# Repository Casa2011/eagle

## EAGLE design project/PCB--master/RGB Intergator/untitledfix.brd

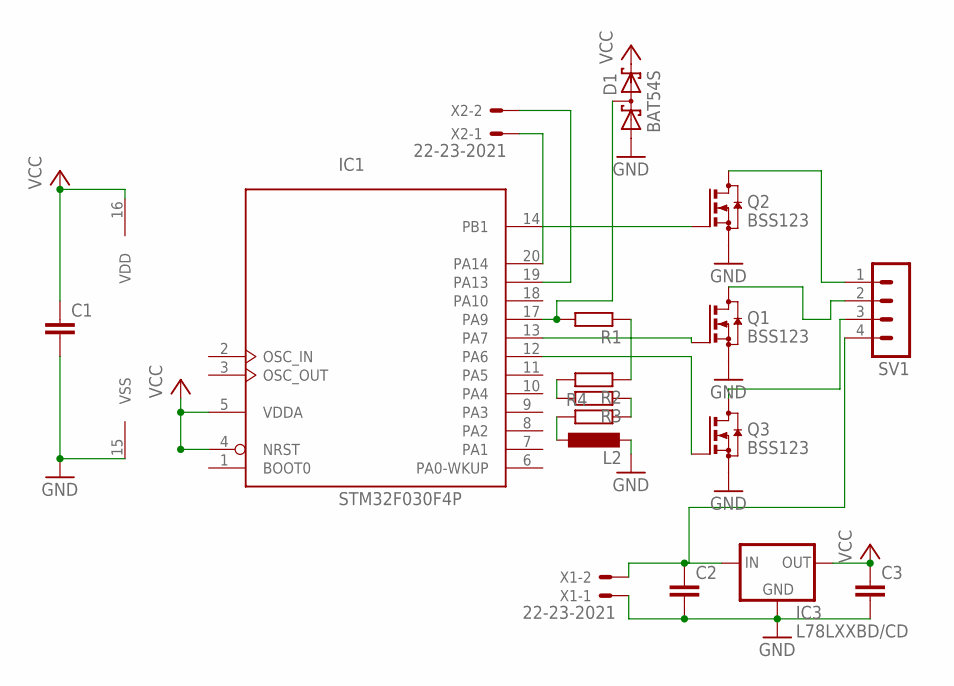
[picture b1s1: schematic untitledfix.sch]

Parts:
C1, C2, C3: C-EUC0805K; C0805K
D1: BAT54S; SOT23
IC1: STM32F030F4P; TSSOP20-I
IC3: L78LXXBD/CD; SO08
L2: L-EU0207/5V; 0207/5V
Q1, Q2, Q3: BSS123; SOT23
R1, R2, R3, R4: R-EU_M0805; M0805
SV1: MA04-1
X1, X2: 22-23-2021

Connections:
GND: C1.2, C2.2, C3.2, D1.1 (A1), IC1.15 (VSS), IC3.2 (GND1), IC3.3 (GND3), IC3.6 (GND4), IC3.7 (GND2), L2.2, Q1.2 (S), Q2.2 (S), Q3.2 (S), X1.1
unnamed: D1.3 (C1A2), IC1.17 (PA9), R1.2
unnamed: IC1.14 (PB1), Q2.1 (G)
unnamed: IC1.13 (PA7), Q1.1 (G)
unnamed: IC1.12 (PA6), Q3.1 (G)
unnamed: C2.1, IC3.8 (IN), SV1.4, X1.2
unnamed: R1.1, R2.1
unnamed: IC1.19 (PA13), X2.2
unnamed: Q3.3 (D), SV1.3
unnamed: Q1.3 (D), SV1.2
unnamed: Q2.3 (D), SV1.1
unnamed: IC1.20 (PA14), X2.1
unnamed: R2.2, R3.2
unnamed: R3.1, R4.2
unnamed: L2.1, R4.1
VCC: C1.1, C3.1, D1.2 (C2), IC1.4 (NRST), IC1.5 (VDDA), IC1.16 (VDD), IC3.1 (OUT)

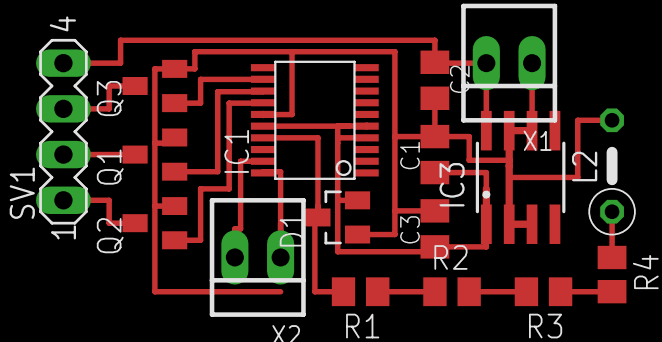
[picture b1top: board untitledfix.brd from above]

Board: 2 copper layers, 17 parts (0 on the bottom side), 16 nets.

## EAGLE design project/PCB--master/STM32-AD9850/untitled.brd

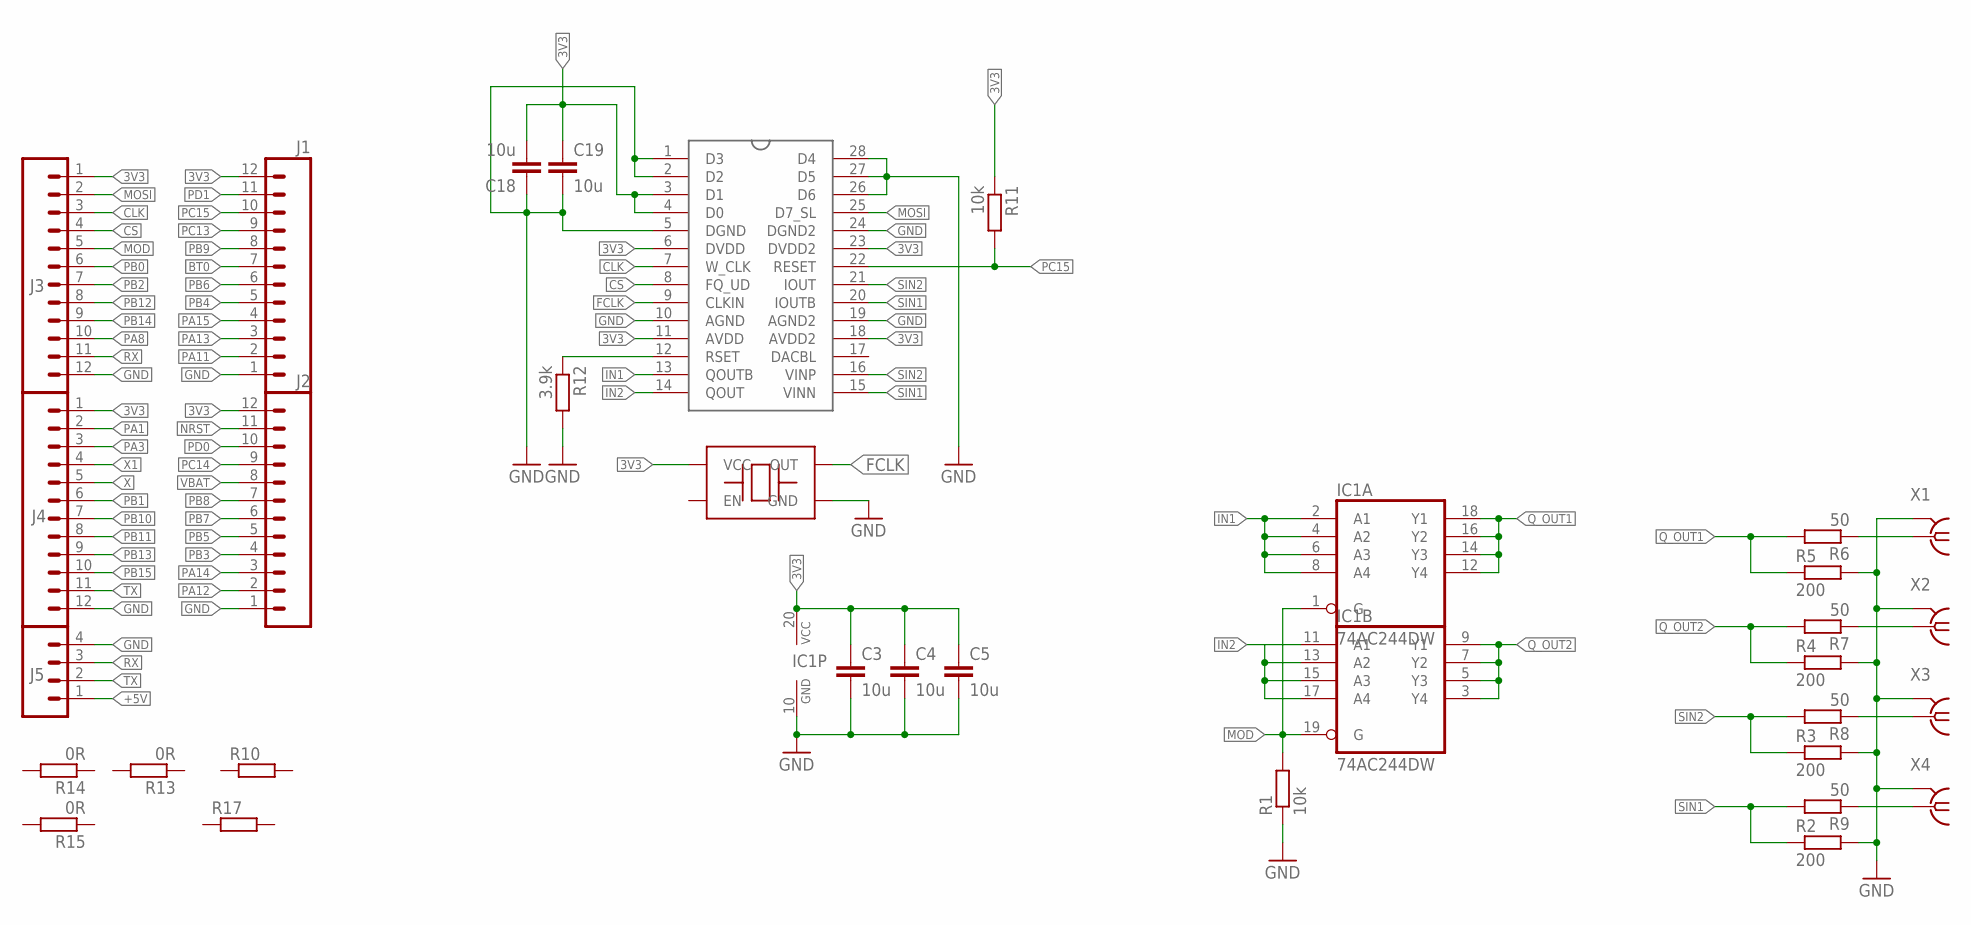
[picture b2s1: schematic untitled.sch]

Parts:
C3, C4, C5, C18, C19: 10u; 0805
IC1: 74AC244DW; SO20W
J1, J2, J3, J4: M12PTH; 1X12
J5: M04PTH; 1X04
R1, R11: 10k; 0805
R2, R3, R4, R5: 200; 0805
R6, R7, R8, R9: 50; 0805
R10: R0805; 0805
R12: 3.9k; 0805
R13, R15: 0R; 0805
R14: 0R; 1206
R17: R1206; 1206
U$1: AD9850; SSOP28
U$3: TXC-BA; 7X5
X1, X2, X3, X4: BU-SMA-H

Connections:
3V3: C3.1, C4.1, C5.1, C18.2, C19.1, IC1.20 (VCC), J1.12, J2.12, J3.1, J4.1, R11.1, U$1.3 (D1), U$1.4 (D0), U$1.6 (DVDD), U$1.11 (AVDD), U$1.18 (AVDD2), U$1.23 (DVDD2), U$3.VCC
+5V: J5.1
BT0: J1.7
CLK: J3.3, U$1.7 (W_CLK)
CS: J3.4, U$1.8 (FQ_UD)
FCLK: U$1.9 (CLKIN), U$3.OUT
GND: C3.2, C4.2, C5.2, C18.1, C19.2, IC1.10 (GND), J1.1, J2.1, J3.12, J4.12, J5.4, R1.1, R2.2, R3.2, R4.2, R5.2, R12.2, U$1.1 (D3), U$1.2 (D2), U$1.5 (DGND), U$1.10 (AGND), U$1.19 (AGND2), U$1.24 (DGND2), U$1.26 (D6), U$1.27 (D5), U$1.28 (D4), U$3.GND, X1.2, X1.3 (2), X1.4 (2), X1.5 (2), X2.2, X2.3 (2), X2.4 (2), X2.5 (2), X3.2, X3.3 (2), X3.4 (2), X3.5 (2), X4.2, X4.3 (2), X4.4 (2), X4.5 (2)
IN1: IC1.2 (A1), IC1.4 (A2), IC1.6 (A3), IC1.8 (A4), U$1.13 (QOUTB)
IN2: IC1.11 (A1), IC1.13 (A2), IC1.15 (A3), IC1.17 (A4), U$1.14 (QOUT)
MOD: IC1.1 (G), IC1.19 (G), J3.5, R1.2
MOSI: J3.2, U$1.25 (D7_SL)
unnamed: R6.1, X1.1
unnamed: R7.1, X2.1
unnamed: R8.1, X3.1
unnamed: R9.1, X4.1
NRST: J2.11
PA1: J4.2
PA3: J4.3
PA8: J3.10
PA11: J1.2
PA12: J2.2
PA13: J1.3
PA14: J2.3
PA15: J1.4
PB0: J3.6
PB1: J4.6
PB2: J3.7
PB3: J2.4
PB4: J1.5
PB5: J2.5
PB6: J1.6
PB7: J2.6
PB8: J2.7
PB9: J1.8
PB10: J4.7
PB11: J4.8
PB12: J3.8
PB13: J4.9
PB14: J3.9
PB15: J4.10
PC13: J1.9
PC14: J2.9
PC15: J1.10, R11.2, U$1.22 (RESET)
PD0: J2.10
PD1: J1.11
Q_OUT1: IC1.12 (Y4), IC1.14 (Y3), IC1.16 (Y2), IC1.18 (Y1), R5.1, R6.2
Q_OUT2: IC1.3 (Y4), IC1.5 (Y3), IC1.7 (Y2), IC1.9 (Y1), R4.1, R7.2
RX: J3.11, J5.3
R_SET: R12.1, U$1.12 (RSET)
SIN1: R2.1, R9.2, U$1.15 (VINN), U$1.20 (IOUTB)
SIN2: R3.1, R8.2, U$1.16 (VINP), U$1.21 (IOUT)
TX: J4.11, J5.2
VBAT: J2.8
X: J4.5
X1: J4.4

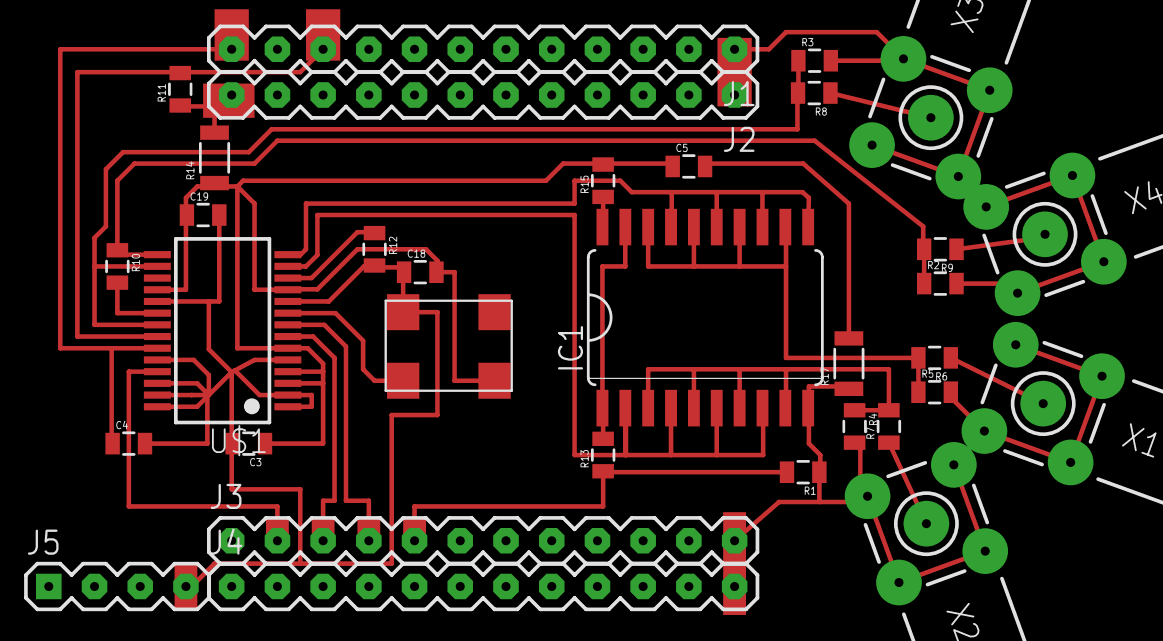
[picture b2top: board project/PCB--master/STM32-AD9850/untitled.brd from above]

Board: 2 copper layers, 33 parts (0 on the bottom side), 21 nets.

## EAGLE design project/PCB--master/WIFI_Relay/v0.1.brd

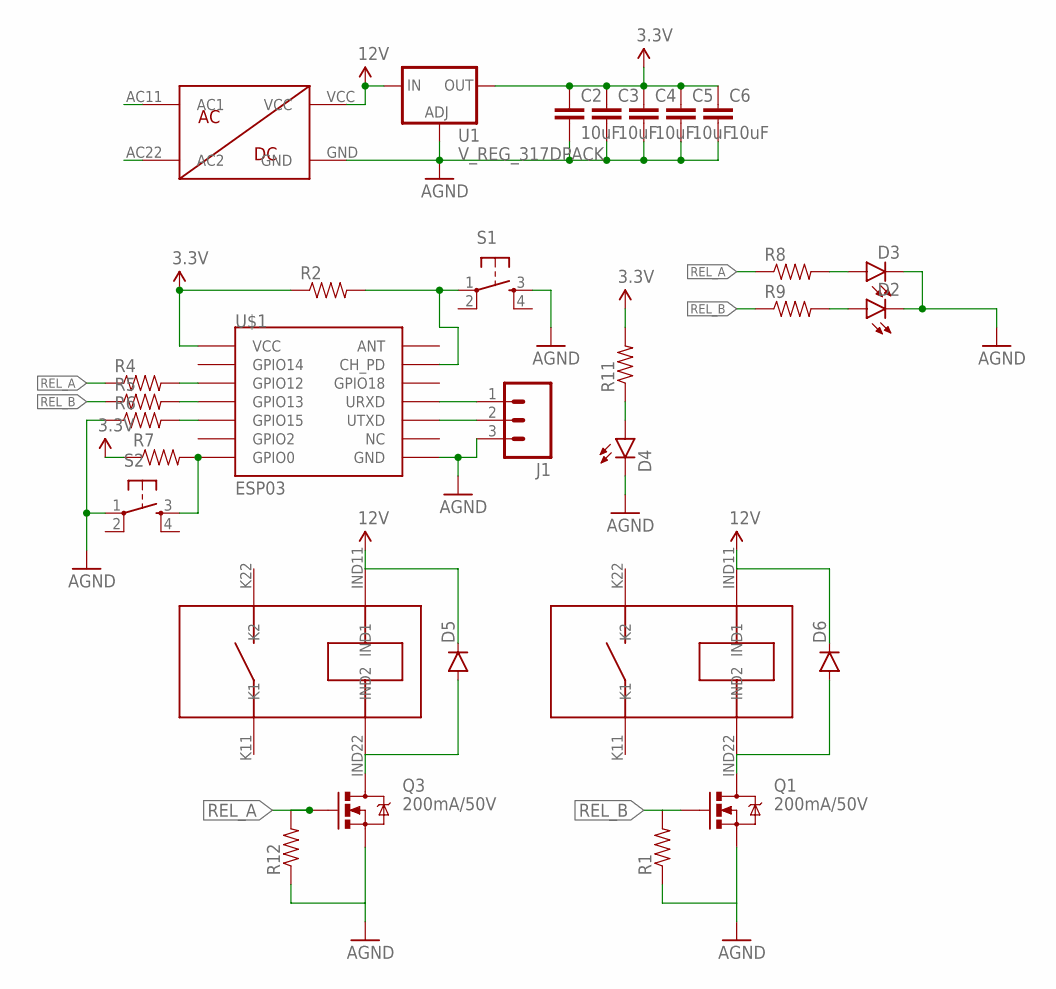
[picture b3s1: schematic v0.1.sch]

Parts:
C2, C3, C4, C5, C6: 10uF; 0603-CAP
D2, D3, D4: LED0603; LED-0603
D5, D6: DIODESOD123; SOD-123
J1: M03LONGPADS; 1X03_LONGPADS
Q1, Q3: 200mA/50V; SOT23-3
R1, R2, R4, R5, R6, R7, R8, R9, R11, R12: RESISTOR0805-RES; 0805
S1, S2: TAC_SWITCHPTH; TACTILE-PTH
U1: V_REG_317DPACK; V-REG_DPACK
U$1: ESP03
U$8: ACDC12V350MA
U$9, U$10: 302WP

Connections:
3.3V: C2.1, C3.1, C4.1, C5.1, C6.1, R2.1, R7.1, R11.2, U1.4 (OUT), U$1.VCC
12V: D5.C, D6.C, U1.3 (IN), U$8.VCC, U$9.IND11 (IND1), U$10.IND11 (IND1)
AGND: C2.2, C3.2, C4.2, C5.2, C6.2, D2.C, D3.C, D4.C, J1.3, Q1.2 (S), Q3.2 (S), R1.1, R6.1, R12.1, S1.3, S2.1, U1.1 (ADJ), U$1.GND, U$8.GND
unnamed: J1.1, U$1.URXD
unnamed: J1.2, U$1.UTXD
unnamed: D5.A, Q3.3 (D), U$10.IND22 (IND2)
unnamed: R2.2, S1.1, U$1.CH_PD
unnamed: R4.2, U$1.GPIO12
unnamed: R5.2, U$1.GPIO13
unnamed: R6.2, U$1.GPIO15
unnamed: D3.A, R8.2
unnamed: D2.A, R9.2
unnamed: R7.2, S2.3, U$1.GPIO0
unnamed: D4.A, R11.1
unnamed: D6.A, Q1.3 (D), U$9.IND22 (IND2)
REL_A: Q3.1 (G), R4.1, R8.1, R12.2
REL_B: Q1.1 (G), R1.2, R5.1, R9.1

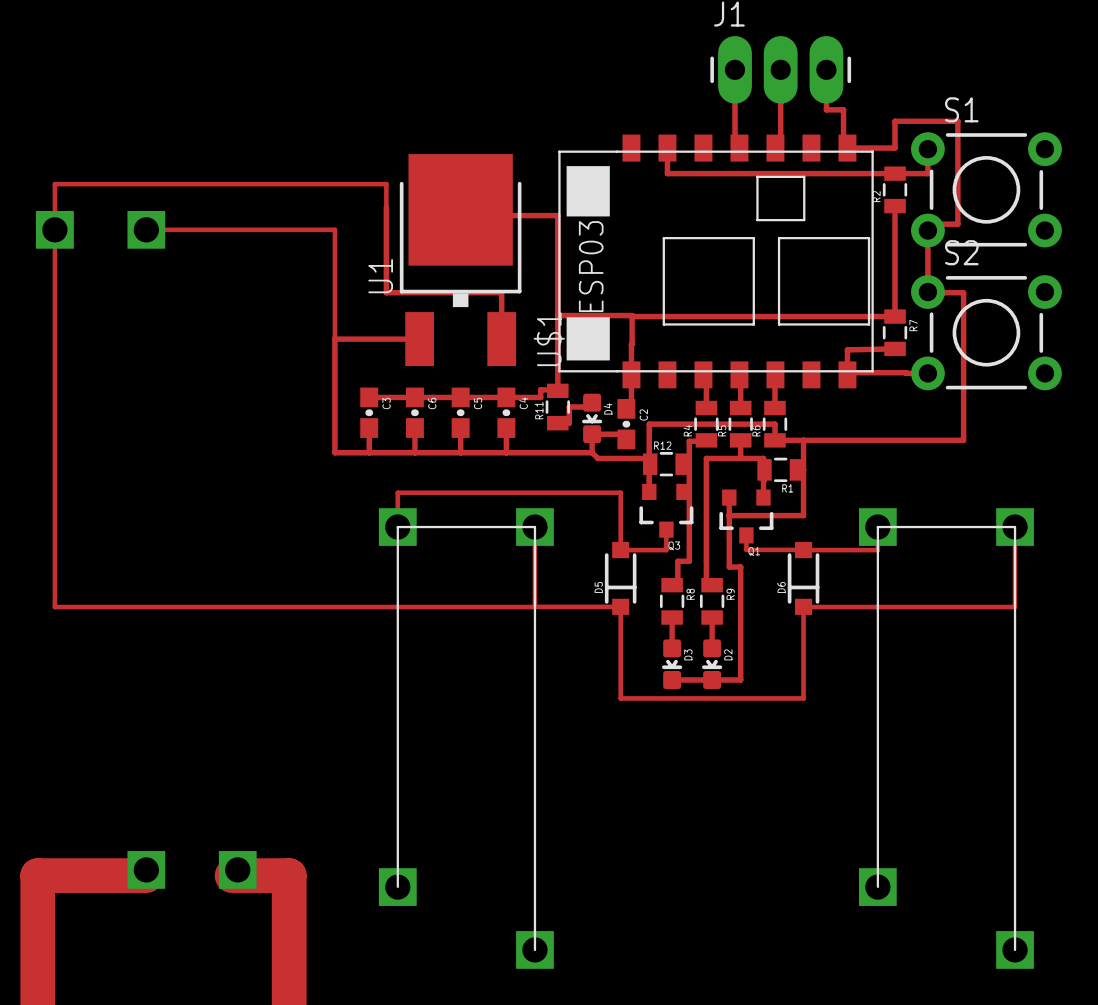
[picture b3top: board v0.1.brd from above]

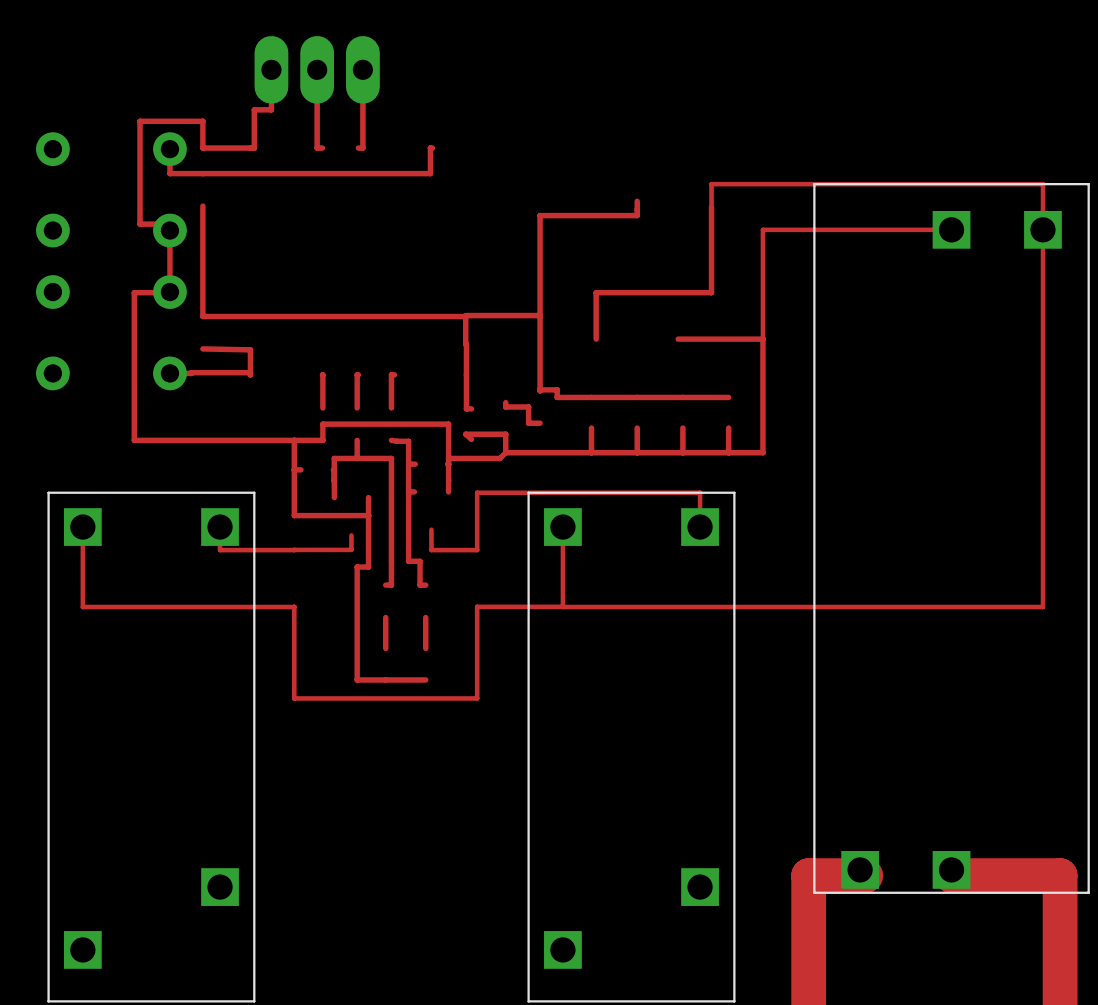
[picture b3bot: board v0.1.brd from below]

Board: 2 copper layers, 30 parts (3 on the bottom side), 17 nets.

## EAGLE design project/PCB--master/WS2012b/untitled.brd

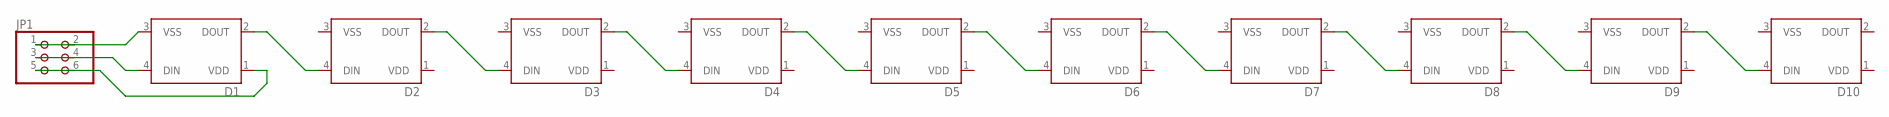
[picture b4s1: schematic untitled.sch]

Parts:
D1, D2, D3, D4, D5, D6, D7, D8, D9, D10: WS2812B
JP1: PINHD-2X03_2.54-SMD; 2X03SMD

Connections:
unnamed: D1.2 (DOUT), D2.4 (DIN)
unnamed: D2.2 (DOUT), D3.4 (DIN)
unnamed: D3.2 (DOUT), D4.4 (DIN)
unnamed: D4.2 (DOUT), D5.4 (DIN)
unnamed: D5.2 (DOUT), D6.4 (DIN)
unnamed: D6.2 (DOUT), D7.4 (DIN)
unnamed: D7.2 (DOUT), D8.4 (DIN)
unnamed: D8.2 (DOUT), D9.4 (DIN)
unnamed: D9.2 (DOUT), D10.4 (DIN)
unnamed: D1.4 (DIN), JP1.3, JP1.4
unnamed: D1.1 (VDD), JP1.5, JP1.6
VDD: D2.1 (VDD), D3.1 (VDD), D4.1 (VDD), D5.1 (VDD), D6.1 (VDD), D7.1 (VDD), D8.1 (VDD), D9.1 (VDD), D10.1 (VDD)
VSS: D1.3 (VSS), D2.3 (VSS), D3.3 (VSS), D4.3 (VSS), D5.3 (VSS), D6.3 (VSS), D7.3 (VSS), D8.3 (VSS), D9.3 (VSS), D10.3 (VSS), JP1.1, JP1.2

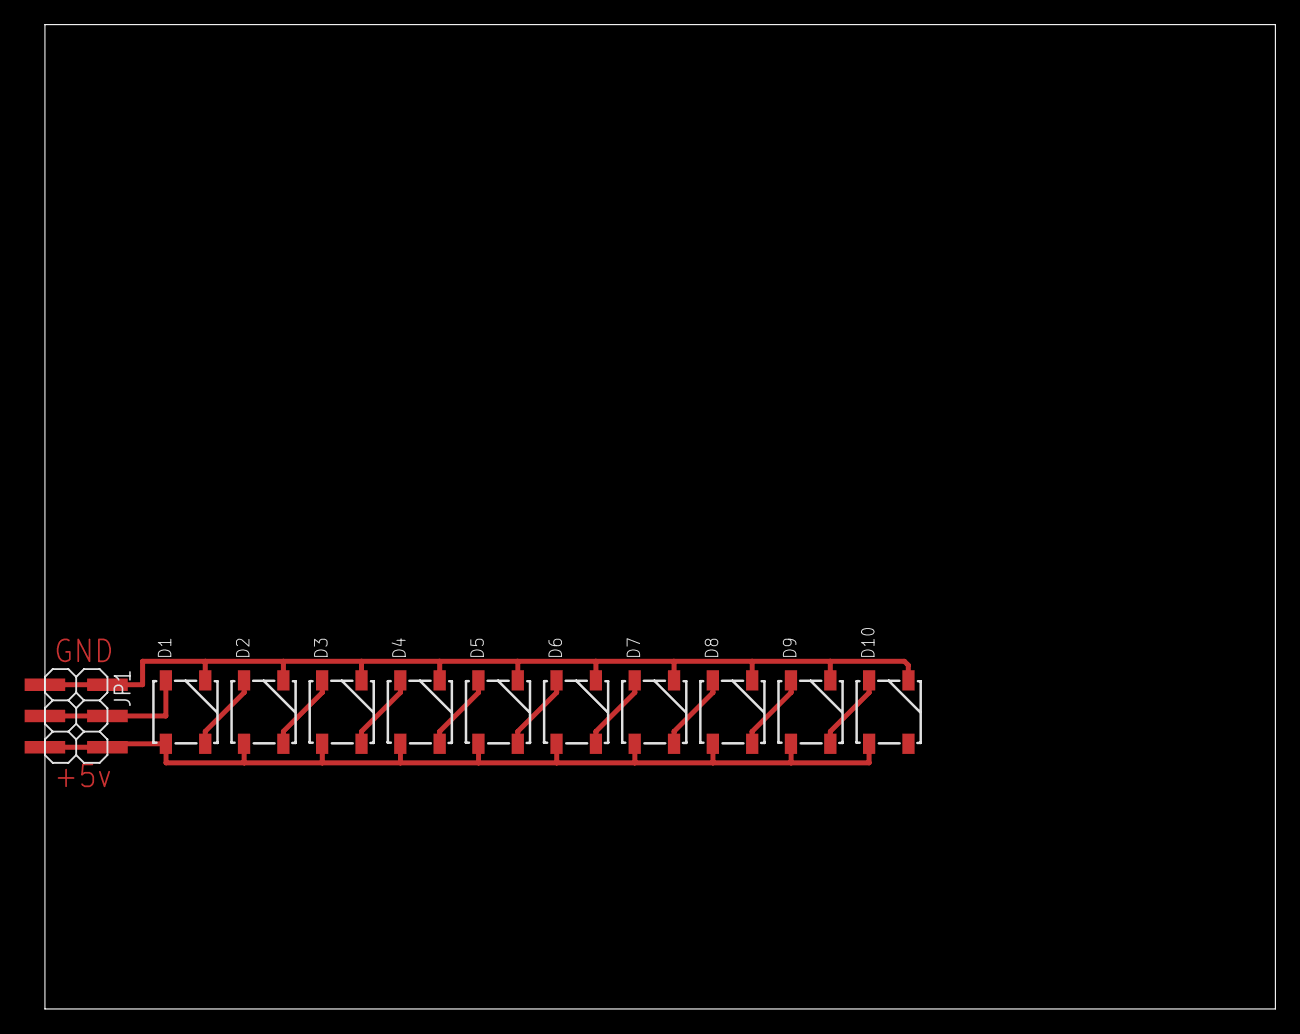
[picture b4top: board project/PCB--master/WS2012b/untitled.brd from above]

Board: 2 copper layers, 100.0 x 80.0 mm, 11 parts (0 on the bottom side), 13 nets.

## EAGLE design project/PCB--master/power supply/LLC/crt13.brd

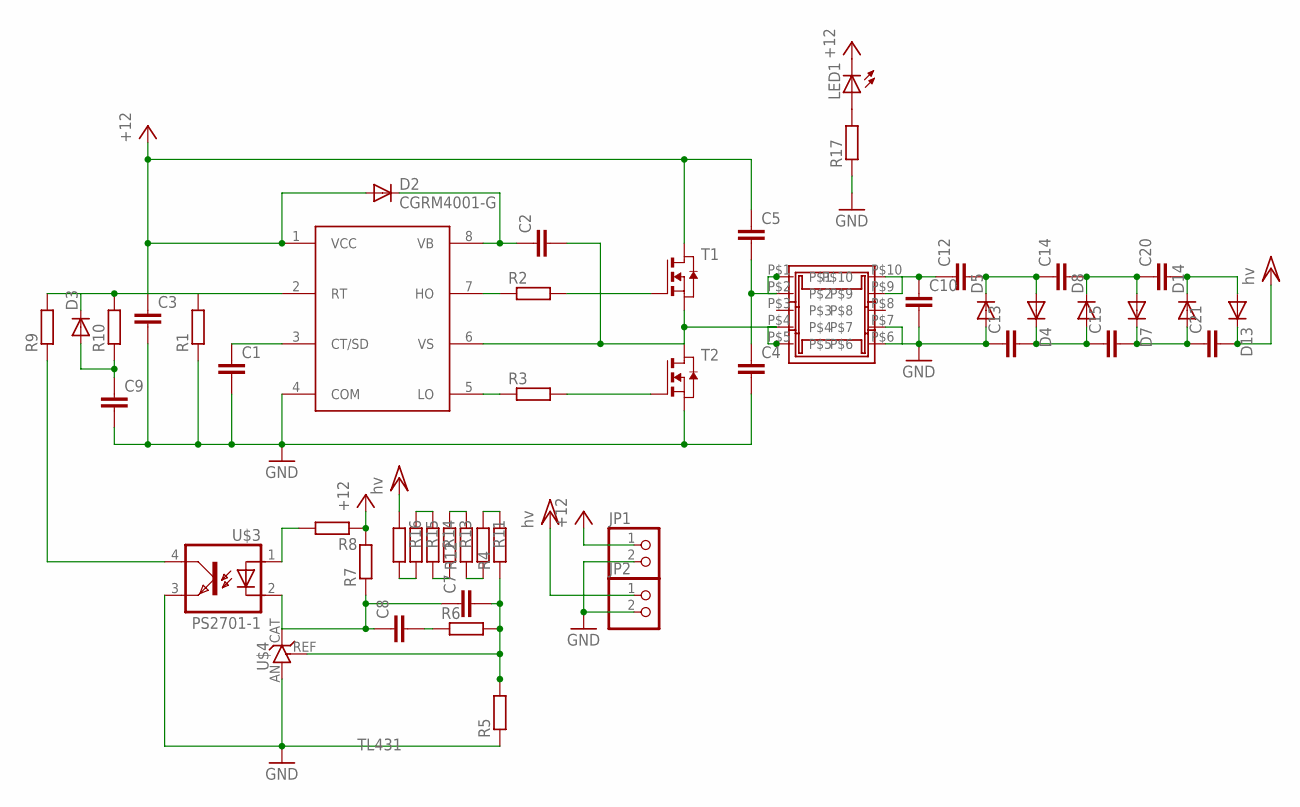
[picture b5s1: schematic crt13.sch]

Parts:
C1, C2, C7, C8: C-EUC0805; C0805
C3, C9: C-EUC1206; C1206
C4, C5: CC1206; C1206
C10: C-EUC1812; C1812
C12, C13, C14, C15, C20, C21: C-EUC2220K; C2220K
D2: CGRM4001-G; SOD-123_MINI-SMA
D3: DIODE-SOD80C; SOD80C
D4, D5, D7, D8, D13, D14: DIODE-DO-214AC; DO-214AC
JP1, JP2: PINHD-1X2; 1X02
LED1: LEDCHIP-LED0805; CHIP-LED0805
R1, R2, R3, R4, R5, R6, R7, R8, R9, R10, R11, R12, R13, R14, R15, R16, R17: R-EU_R0805; R0805
T1, T2: NMOSSOT23; SOT-23
U$1: IRS2795; SO08
U$2: EFD15-K-10P; EFD15-K10P
U$3: PS2701-1; SOP04
U$4: TL431; SOT23

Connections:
GND: C1.2, C3.2, C4.2, C9.2, C10.2, C13.1, D5.A, JP1.2, JP2.2, R1.1, R5.1, R17.1, T2.2 (S), U$1.4 (COM), U$2.P$6, U$2.P$7, U$3.3, U$4.AN
unnamed: R8.2, U$3.1
unnamed: C2.1, D2.C, U$1.8 (VB)
unnamed: C1.1, U$1.3 (CT/SD)
unnamed: LED1.A, R17.2
unnamed: D3.C, R1.2, R9.2, R10.2, U$1.2 (RT)
unnamed: R3.1, U$1.5 (LO)
unnamed: R2.1, U$1.7 (HO)
unnamed: C2.2, T1.2 (S), T2.1 (D), U$1.6 (VS), U$2.P$4, U$2.P$5
unnamed: R3.2, T2.3 (G)
unnamed: R2.2, T1.3 (G)
unnamed: C7.2, R4.1, R5.2, R6.2, U$4.REF
unnamed: C8.2, R6.1
unnamed: C7.1, C8.1, R7.1, U$3.2, U$4.CAT
unnamed: R9.1, U$3.4
unnamed: R4.2, R11.1
unnamed: R11.2, R12.1
unnamed: C10.1, C12.1, U$2.P$9, U$2.P$10
unnamed: R12.2, R13.1
unnamed: C9.1, D3.A, R10.1
unnamed: C12.2, C14.1, D4.A, D5.C
unnamed: R13.2, R14.2
unnamed: R14.1, R15.1
unnamed: R15.2, R16.2
unnamed: C13.2, C15.1, D4.C, D8.A
unnamed: C14.2, C20.1, D7.A, D8.C
unnamed: C20.2, D13.A, D14.C
unnamed: C15.2, C21.1, D7.C, D14.A
unnamed: C4.1, C5.2, U$2.P$1, U$2.P$2
VCC: C3.1, C5.1, D2.A, JP1.1, LED1.C, R7.2, R8.1, T1.1 (D), U$1.1 (VCC)
VCC/2: C21.2, D13.C, JP2.1, R16.1

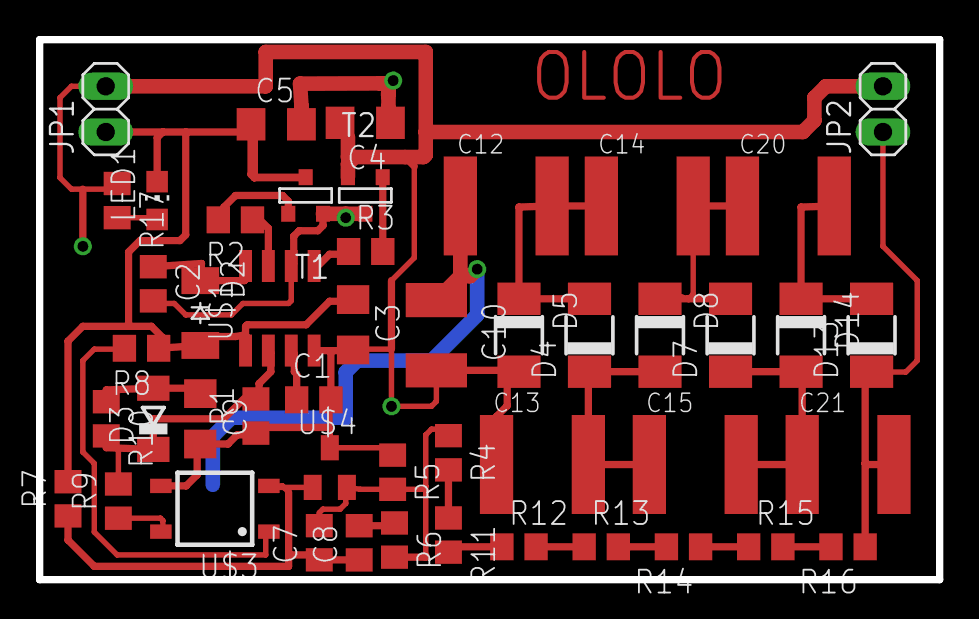
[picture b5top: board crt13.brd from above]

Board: 2 copper layers, 50.0 x 30.0 mm, 49 parts (1 on the bottom side), 31 nets.

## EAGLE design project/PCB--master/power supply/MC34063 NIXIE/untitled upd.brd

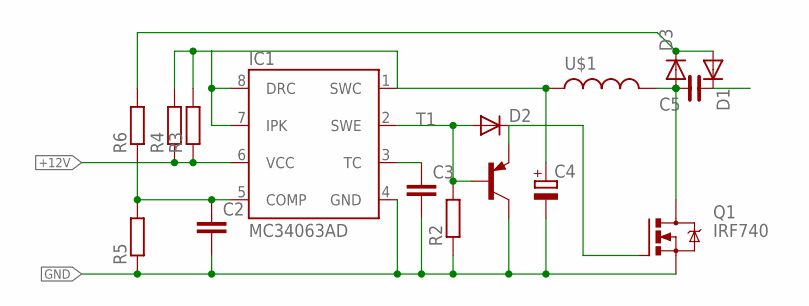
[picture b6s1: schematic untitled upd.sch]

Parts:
C2, C3: C-EUC0805K; C0805K
C4: CPOL-EU153CLV-0605; 153CLV-0605
C5: C_0805; C0805
D1, D2, D3: DIODE-DO-214AC; DO-214AC
IC1: MC34063AD; SO08
Q1: IRF740; TO220BV
R2, R3, R4, R5, R6: R-EU_M0805; M0805
T1: BC807-16-PNP-SOT23-BEC; SOT23-BEC
U$1: MSS1260

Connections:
+12V: IC1.6 (VCC), R3.1, R4.1
GND: C2.2, C3.2, C4.-, IC1.4 (GND), Q1.S, R2.1, R5.1, T1.C
unnamed: C5.1, D1.C
unnamed: D2.C, Q1.G, T1.E
unnamed: D2.A, IC1.2 (SWE), R2.2, T1.B
unnamed: C4.+, IC1.1 (SWC), IC1.7 (IPK), IC1.8 (DRC), R3.2, R4.2, U$1.P$2
unnamed: C3.1, IC1.3 (TC)
unnamed: C2.1, IC1.5 (COMP), R5.2, R6.1
unnamed: D1.A, D3.C, R6.2
unnamed: C5.2, D3.A, Q1.D, U$1.P$1

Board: 2 copper layers, 16 parts (0 on the bottom side), 10 nets, no tracks yet.

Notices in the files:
parts and their libraries:
SparkFun-Aesthetics: Licensing: Creative Commons ShareAlike 4.0 International - https://creativecommons.org/licenses/by-sa/4.0
rc-master: Copyright (C) 2007, Bob Starr
